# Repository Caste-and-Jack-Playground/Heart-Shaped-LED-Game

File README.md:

# Heart-Shaped-LED-Game
This cute game will test your reflexes and rythm.\
It's pretty easy to use, there are just two buttons for two players.
The goal is to press the button when the leds on the top are at their maximum or minimum brightness.\
When you win, the leds on your side will blink.\
Then you'll get to the next level where the leds will fade on and off even faster.\
This game can be played alone, with a friend or maybe even a lover.

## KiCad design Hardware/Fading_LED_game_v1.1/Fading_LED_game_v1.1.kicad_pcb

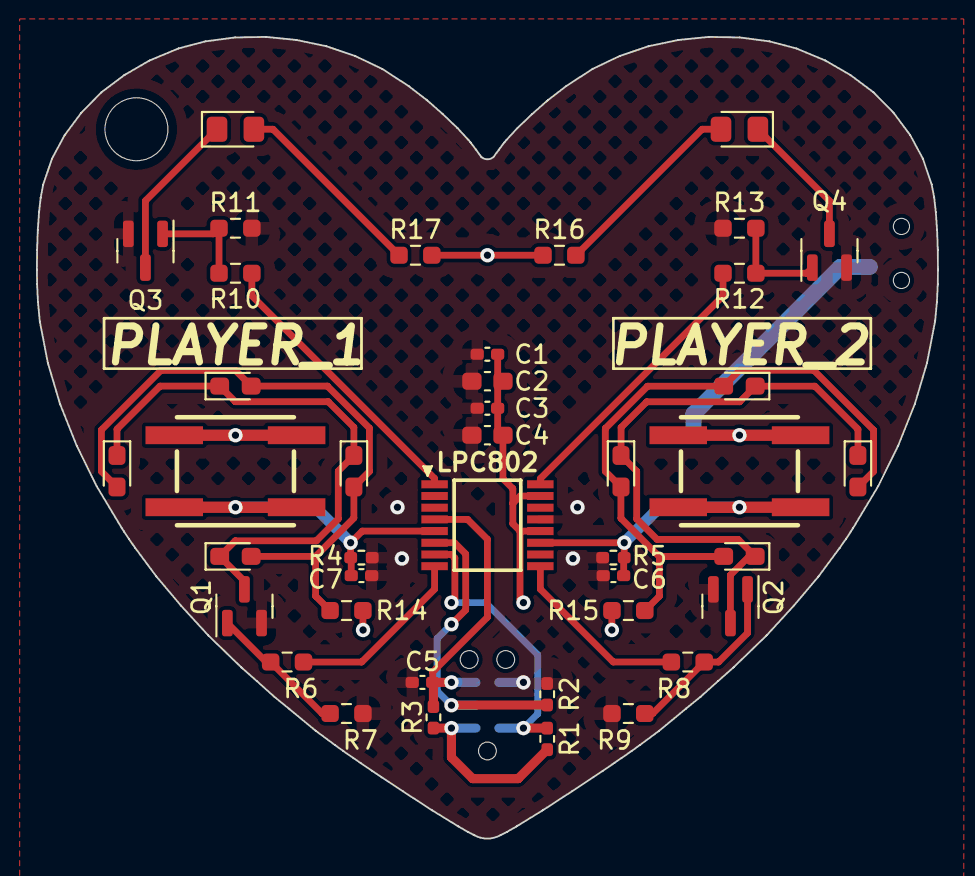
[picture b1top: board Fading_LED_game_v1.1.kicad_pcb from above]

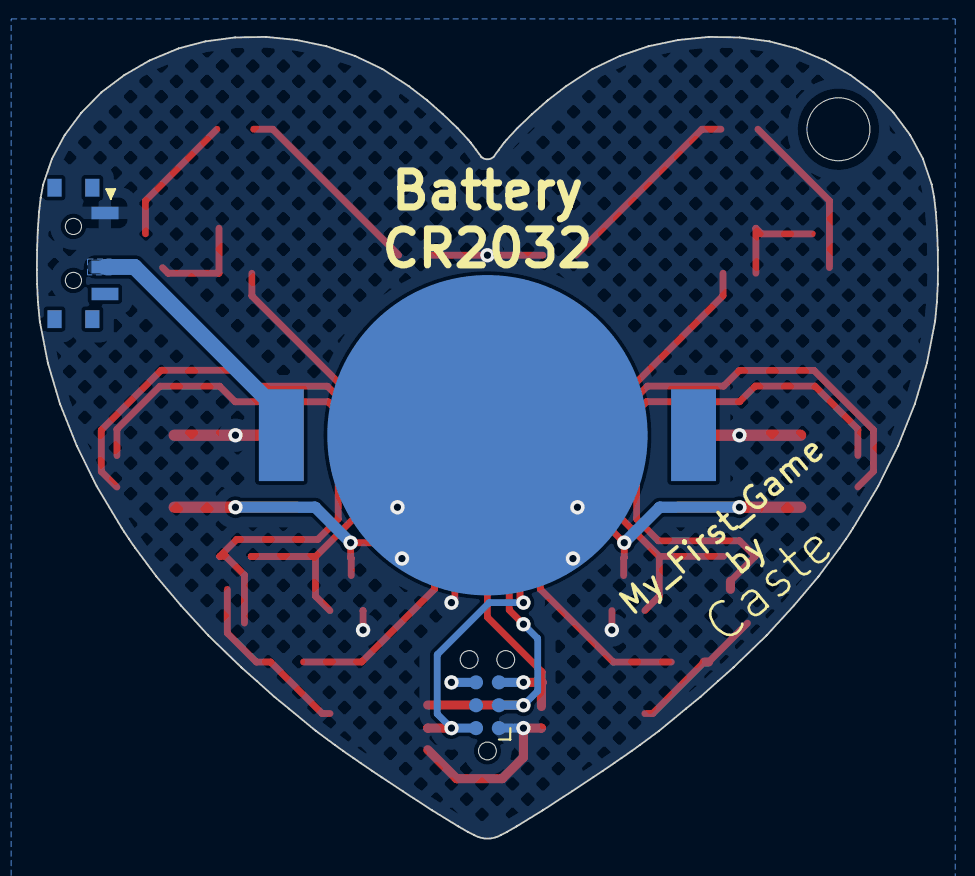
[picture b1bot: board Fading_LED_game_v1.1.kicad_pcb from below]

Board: 2 copper layers, 50.1 x 44.5 mm, 44 parts (3 on the bottom side), 24 nets.

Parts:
BT1: CR2032_BAT-HLD-001
C1, C3, C5, C6, C7: 100nF 50V; C_0402_1005Metric_Pad0.74x0.62mm_HandSolder
C2, C4: 10uF 10V; C_0603_1608Metric_Pad1.08x0.95mm_HandSolder
D1: PINK_LED_P1; LED_0603_1608Metric_Pad1.05x0.95mm_HandSolder
D2, D3, D4: LED_P1; LED_0603_1608Metric_Pad1.05x0.95mm_HandSolder
D5, D6, D7, D8: LED_P2; LED_0603_1608Metric_Pad1.05x0.95mm_HandSolder
D9, D10: LED; LED_0805_2012Metric_Pad1.15x1.40mm_HandSolder
J1: Prog conn; Tag-Connect_TC2030-IDC-NL_2x03_P1.27mm_Vertical
LPC802: mcu LPC802M001JDH16J; mcu LPC802
PLAYER_1, PLAYER_2: Button EVQ-Q2K03W; Button EVQ-Q2B03W
Q1, Q2, Q3, Q4: BC817; SOT-23
R1, R2, R3: 10k; R_0402_1005Metric_Pad0.72x0.64mm_HandSolder
R4, R5: 47k; R_0402_1005Metric_Pad0.72x0.64mm_HandSolder
R6, R7, R8, R9, R10, R11, R12, R13: 10k; R_0603_1608Metric_Pad0.98x0.95mm_HandSolder
R14, R15, R16, R17: 750; R_0603_1608Metric_Pad0.98x0.95mm_HandSolder
S1: Switch_CUS-12TB

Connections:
+3V3: C1.2, C2.2, C3.2, C4.2, J1.1 (VCC), LPC802.12 (VDD), LPC802.15 (VREFP), PLAYER_1.1 (A), PLAYER_1.4 (A'), PLAYER_2.1 (A), PLAYER_2.4 (A'), R1.1, R3.1, R14.2, R15.2, R16.2, R17.2, S1.1 (NO)
+BATT: BT1.1 (+_1), S1.2 (COM)
/!RST: C5.2, J1.5 (GND), LPC802.4 (~RESET/PIO0_5), R3.2
/+: C7.2, LPC802.5 (PIO0_4/ADC_11/NTRST), PLAYER_1.2 (B), PLAYER_1.3 (B'), R4.1
/-: C6.2, LPC802.11 (PIO0_8/ADC_5), PLAYER_2.2 (B), PLAYER_2.3 (B'), R5.1
/LEDS_BL: LPC802.8 (PIO0_11/ADC_6/WKTCLKIN), R6.1
/LEDS_BR: LPC802.9 (PIO0_1/ADC_0/ACMP_I2/CLKIN/TDI), R8.1
/LEDS_L: LPC802.1 (PIO0_17/ADC_9), R10.1
/LEDS_R: LPC802.16 (PIO0_0/ACMP_I1/TDO), R12.1
/SWCLK: J1.3 (~RESET), LPC802.6 (PIO0_3/SWCLK/TCK), R2.1
/SWDIO: J1.2 (SWDIO), LPC802.7 (PIO0_2/SWDIO/TMS), R1.2
GND: BT1.3 (-), C1.1, C2.1, C3.1, C4.1, C5.1, C6.1, C7.1, J1.6 (SWO), LPC802.13 (VSS), Q1.2 (E), Q2.2 (E), Q3.2 (E), Q4.2 (E), R2.2, R4.2, R5.2, R7.2, R9.2, R11.2, R13.2
unnamed: D1.2 (A), D2.2 (A), D3.2 (A), D4.2 (A), R14.1
unnamed: D1.1 (K), D2.1 (K), D3.1 (K), D4.1 (K), Q1.3 (C)
unnamed: D5.2 (A), D6.2 (A), D7.2 (A), D8.2 (A), R15.1
unnamed: D5.1 (K), D6.1 (K), D7.1 (K), D8.1 (K), Q2.3 (C)
unnamed: D9.2 (A), R17.1
unnamed: D9.1 (K), Q3.3 (C)
unnamed: D10.2 (A), R16.1
unnamed: D10.1 (K), Q4.3 (C)
unnamed: Q1.1 (B), R6.2, R7.1
unnamed: Q2.1 (B), R8.2, R9.1
unnamed: Q3.1 (B), R10.2, R11.1
unnamed: Q4.1 (B), R12.2, R13.1
